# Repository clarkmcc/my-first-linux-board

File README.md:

# my-first-linux-board

`my-first-linux-board` is a small F1C200S Linux board built around removable microSD storage, USB-C power and USB device data, a 3.3 V UART console, and power/status LEDs. This repository contains the exact KiCad design used for the assembled board, the working Buildroot firmware source, the final JLCPCB fabrication package, and purchasing files.

The assembled board boots U-Boot 2026.01 and Linux 6.19.14 into a minimal BusyBox system. Both boot stages identify it as `Clark's Board`.

## Hardware

| Item | Final design |
|---|---|
| Processor | Allwinner F1C200S with 64 MiB integrated DDR1 |
| Board | 44 × 44 mm, four copper layers, R3 rounded corners |
| Power input | USB-C, 5 V, TPS2553 current-limited input switch |
| Rails | Three TPS62160 bucks for core, DDR, and I/O; TLV75528 analog LDO |
| Storage | Bottom-mounted microSD socket |
| Console | UART0 on a three-pin 3.3 V header: GND, TX, RX |
| USB | Native USB peripheral connection over USB-C |
| Indicators | Fixed power LED and PC0-controlled active-low status LED |
| Assembly | Components on top except the bottom microSD socket; through-hole UART header |
| Finish used | Black solder mask, white silkscreen, ENIG |

Open [hardware/boot-console.kicad_pro](hardware/boot-console.kicad_pro) in KiCad 10. The [BOM](hardware/docs/BOM.md), [pinout](hardware/docs/PINOUT.md), and [component-purpose guide](hardware/docs/COMPONENT-PURPOSE.md) describe the final circuit.

The [schematic PDF](docs/schematic.pdf) and [combined copper-layer image](docs/images/all-copper-layers.png) are convenient read-only views of the same final design.

## Firmware

The firmware directory is a Buildroot external tree. On macOS or another Docker host:

```sh
cd firmware
./build-container.sh
```

The complete card image is generated at:

```text
firmware/output/images/sdcard.img
```

The proven board configuration uses one-bit microSD transfers at 12.5 MHz. The physical board has four data traces, but Linux produced data errors in four-bit/25 MHz mode on the first assembly; the conservative setting boots reliably and is therefore the canonical configuration.

UART0 is 115200 baud, 8 data bits, no parity, and one stop bit. Linux also
creates a composite USB device with a CDC ACM console and a CDC ECM Ethernet
link. The board is `192.168.7.2/24`; its small DHCP server assigns the attached
host an address without advertising a default route or DNS server. On macOS,
the gadget can enumerate before Network Settings creates a service. Find the
interface whose MAC address is `02:00:00:00:07:01`, assign the host side
`192.168.7.1` for immediate access, and ask macOS to detect the new hardware:

```sh
iface=$(for interface in $(ifconfig -l); do
  ifconfig "$interface" | grep -q 'ether 02:00:00:00:07:01' && echo "$interface"
done)
sudo ifconfig "$iface" inet 192.168.7.1 netmask 255.255.255.0 up
sudo networksetup -detectnewhardware
```

This address lasts until the interface is removed or reconfigured. After
`networksetup -detectnewhardware` creates the service, give it the persistent
static address used by this direct link. The service on the tested Mac is named
`Clark's Board Console + Ethernet`:

```sh
sudo networksetup -setmanual "Clark's Board Console + Ethernet" \
  192.168.7.1 255.255.255.0 0.0.0.0
```

If macOS uses a different service name, find it with
`networksetup -listallnetworkservices` and substitute that name. DHCP did not
activate this ECM link reliably, so keep the host address static.

Prometheus metrics are the only HTTP resource. Scrape them with:

```sh
curl http://192.168.7.2/cgi-bin/metrics
```

The endpoint uses the Prometheus 0.0.4 text format and reports board identity,
time, CPU, load, memory, VM, pressure, filesystem, microSD, network, socket,
entropy, LED, service, USB gadget, and available thermal, CPU-frequency, and
watchdog data. The root URL and every other HTTP path intentionally return 404.

SSH is available as `root` with a blank password:

```sh
ssh root@192.168.7.2
```

This passwordless access is intended for a directly attached development
cable. The first boot stores a generated SSH host key on the FAT boot partition
so the host fingerprint remains stable while the read-only root stays unchanged.

The status LED appears at:

```text
/sys/class/leds/boot-console:green:status
```

It uses the CPU `activity` trigger by default. Manual control:

```sh
LED=/sys/class/leds/boot-console:green:status
echo none > "$LED/trigger"
echo 1 > "$LED/brightness"
echo 0 > "$LED/brightness"
```

See [firmware/README.md](firmware/README.md) for build details and [firmware/docs/BRINGUP.md](firmware/docs/BRINGUP.md) for bench bring-up.

## Manufacturing and purchasing

- [fabrication/clarks-board-JLCPCB-gerbers.zip](fabrication/clarks-board-JLCPCB-gerbers.zip) is the exact bare-board package used for the final revision.
- [fabrication/assembly/clarks-board-JLCPCB-BOM.csv](fabrication/assembly/clarks-board-JLCPCB-BOM.csv) and [fabrication/assembly/clarks-board-JLCPCB-CPL.csv](fabrication/assembly/clarks-board-JLCPCB-CPL.csv) are formatted for JLCPCB assembly upload.
- [procurement/DigiKey-order.csv](procurement/DigiKey-order.csv) and [procurement/LCSC-order.csv](procurement/LCSC-order.csv) contain the final supplier split used during sourcing.
- [hardware/assembly/ibom.html](hardware/assembly/ibom.html) is an interactive assembly view.

The fabrication package retains the routed board exactly. USB impedance was not matched to a specific JLCPCB controlled-impedance stackup, so select and verify a stackup before changing USB routing or ordering a controlled-impedance revision.

## Validation status

- The assembled board reaches a Linux login prompt over UART.
- The status LED works through the Linux LED subsystem after correcting duplicate PC0 pin ownership.
- KiCad ERC and DRC pass on the final source.
- The saved fabrication package matches the final KiCad source.
- Power/reset calculations and saved transient results are documented in [docs/POWER-VERIFICATION.md](docs/POWER-VERIFICATION.md).

Generated firmware images, Buildroot downloads, compiler output, KiCad backups, caches, and editor state are intentionally excluded from Git.

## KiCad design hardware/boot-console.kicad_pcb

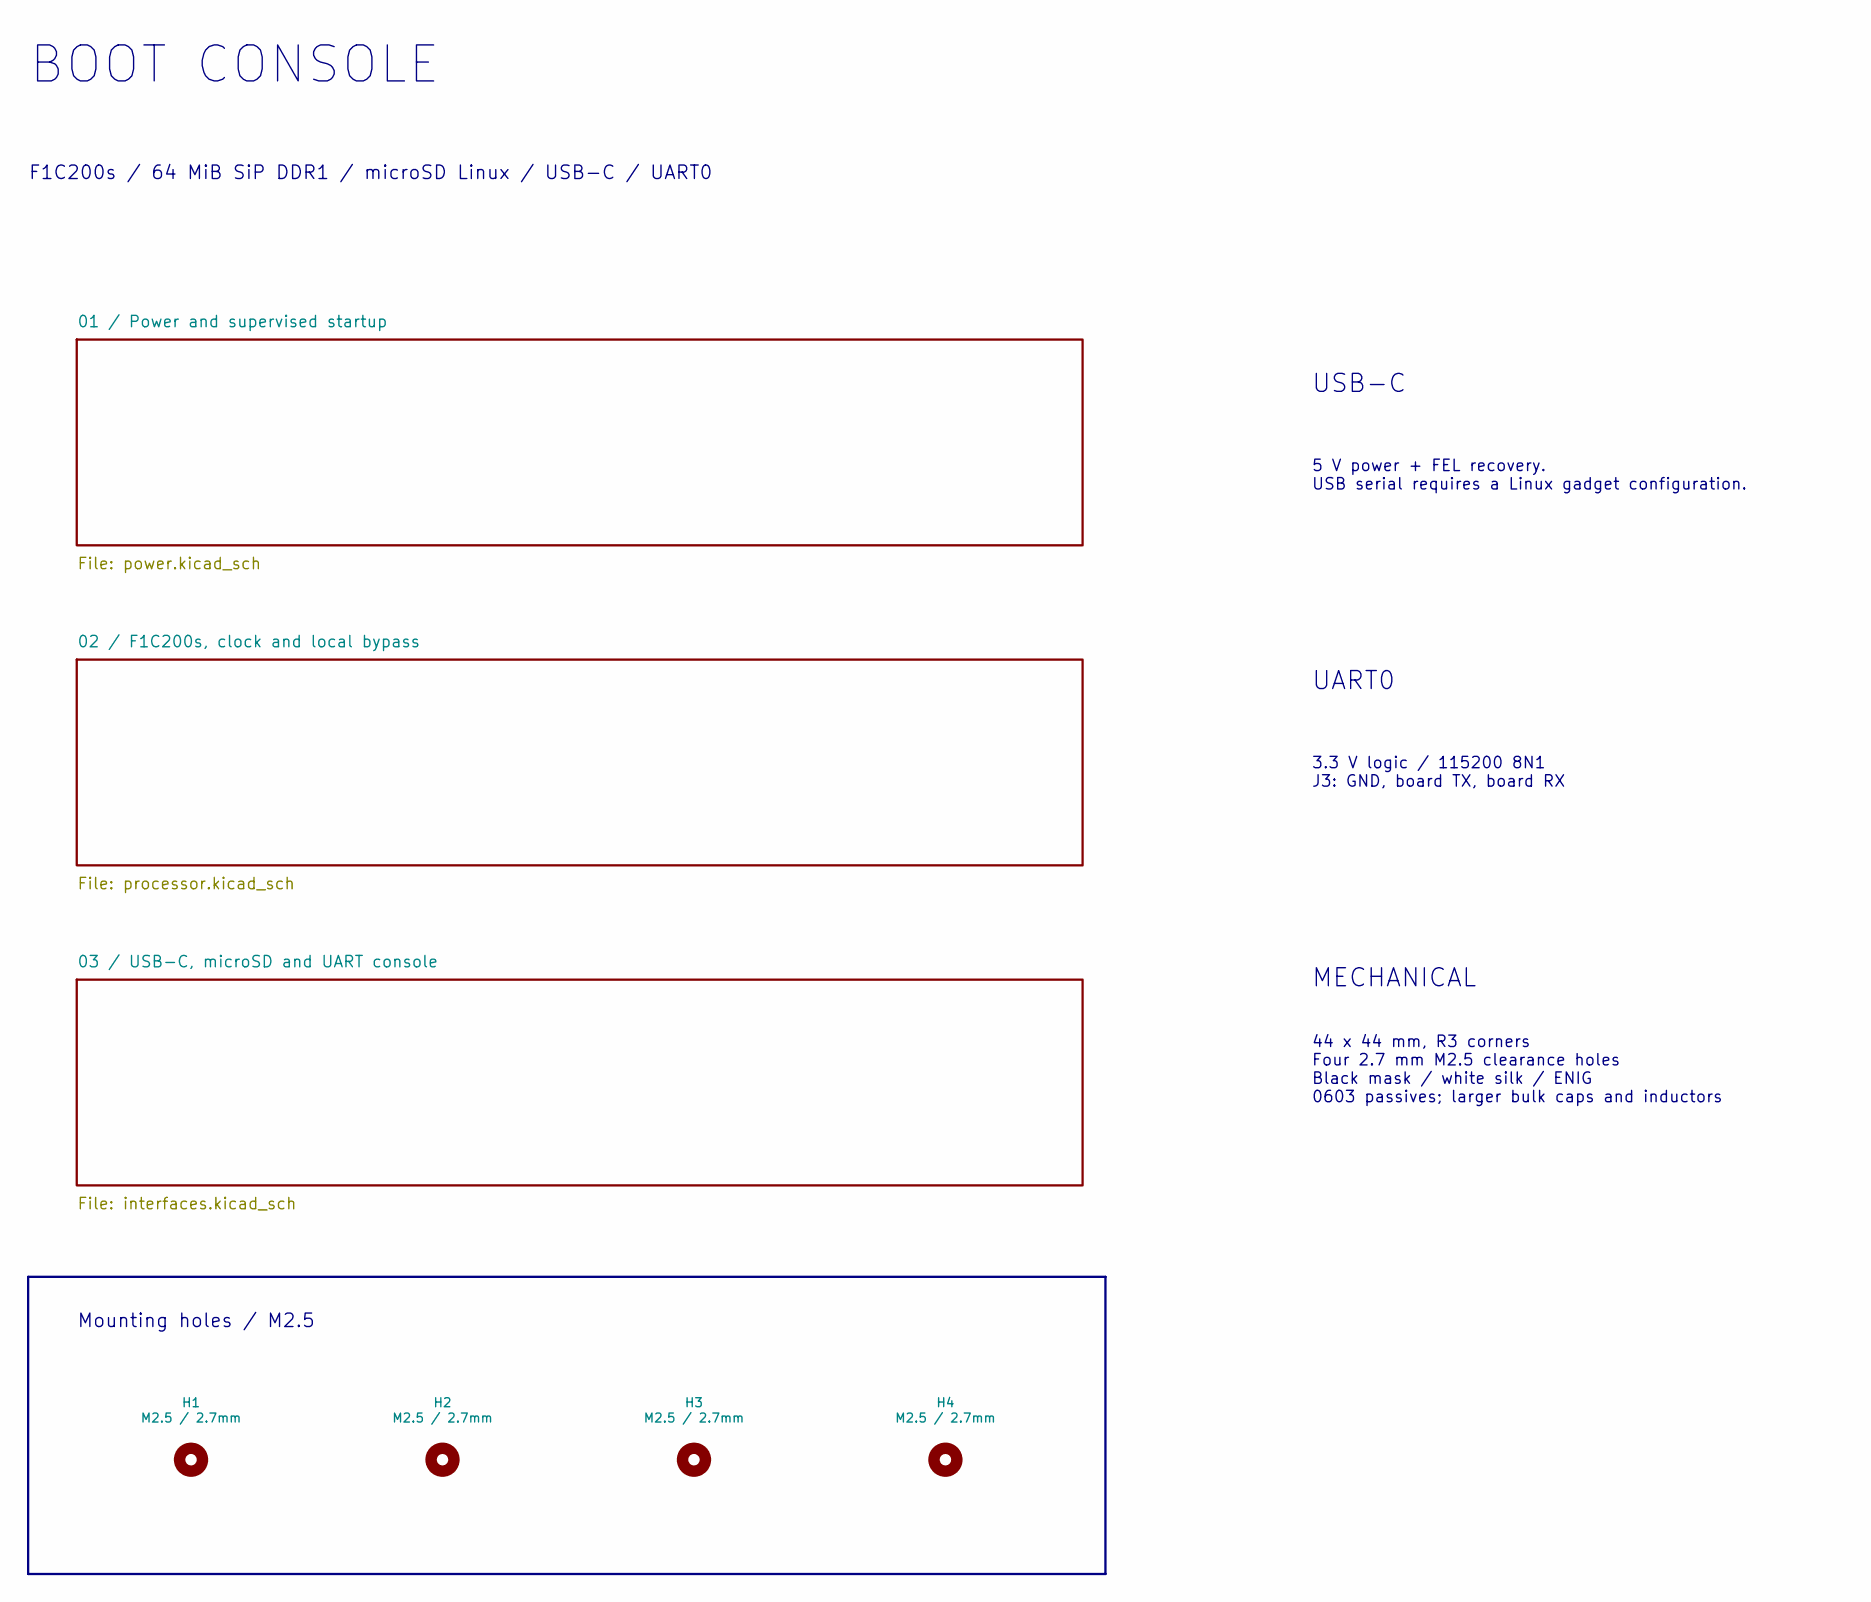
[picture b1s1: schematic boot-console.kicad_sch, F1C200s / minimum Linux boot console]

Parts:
H1, H2, H3, H4: M2.5 / 2.7mm; MountingHole_2.7mm_M2.5

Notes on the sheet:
BOOT CONSOLE
F1C200s / 64 MiB SiP DDR1 / microSD Linux / USB-C / UART0
USB-C
5 V power + FEL recovery. USB serial requires a Linux gadget configuration.
UART0
3.3 V logic / 115200 8N1 J3: GND, board TX, board RX
MECHANICAL
44 x 44 mm, R3 corners Four 2.7 mm M2.5 clearance holes Black mask / white silk / ENIG 0603 passives; larger bulk caps and inductors
Mounting holes / M2.5

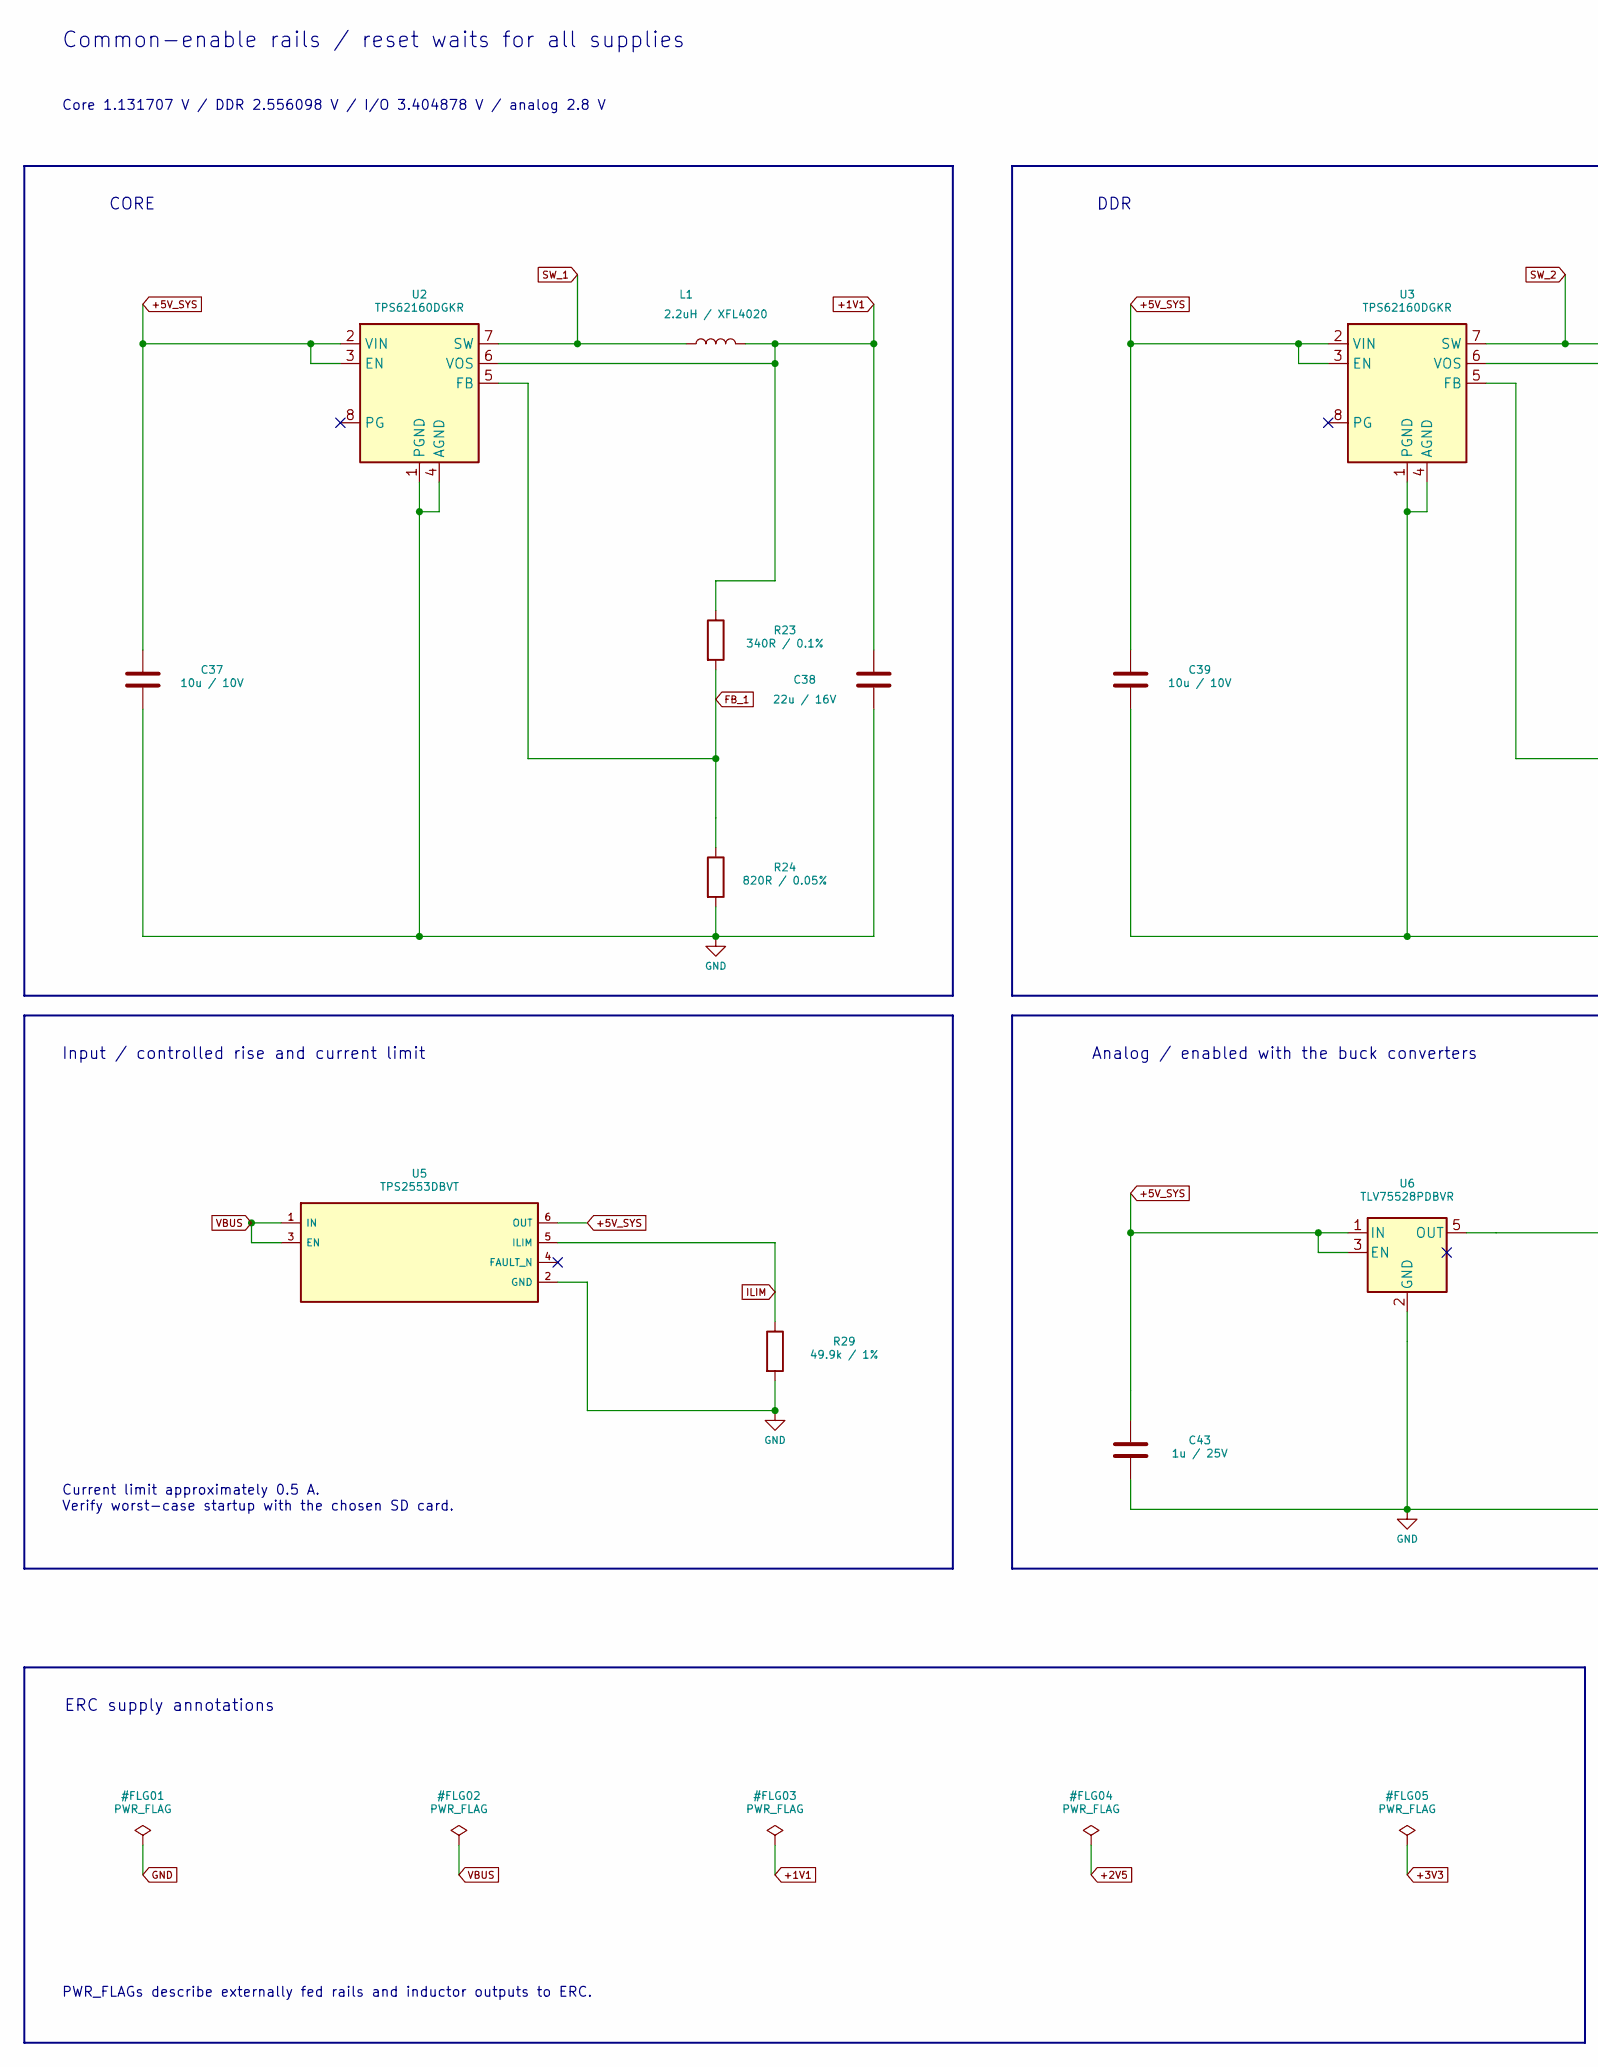
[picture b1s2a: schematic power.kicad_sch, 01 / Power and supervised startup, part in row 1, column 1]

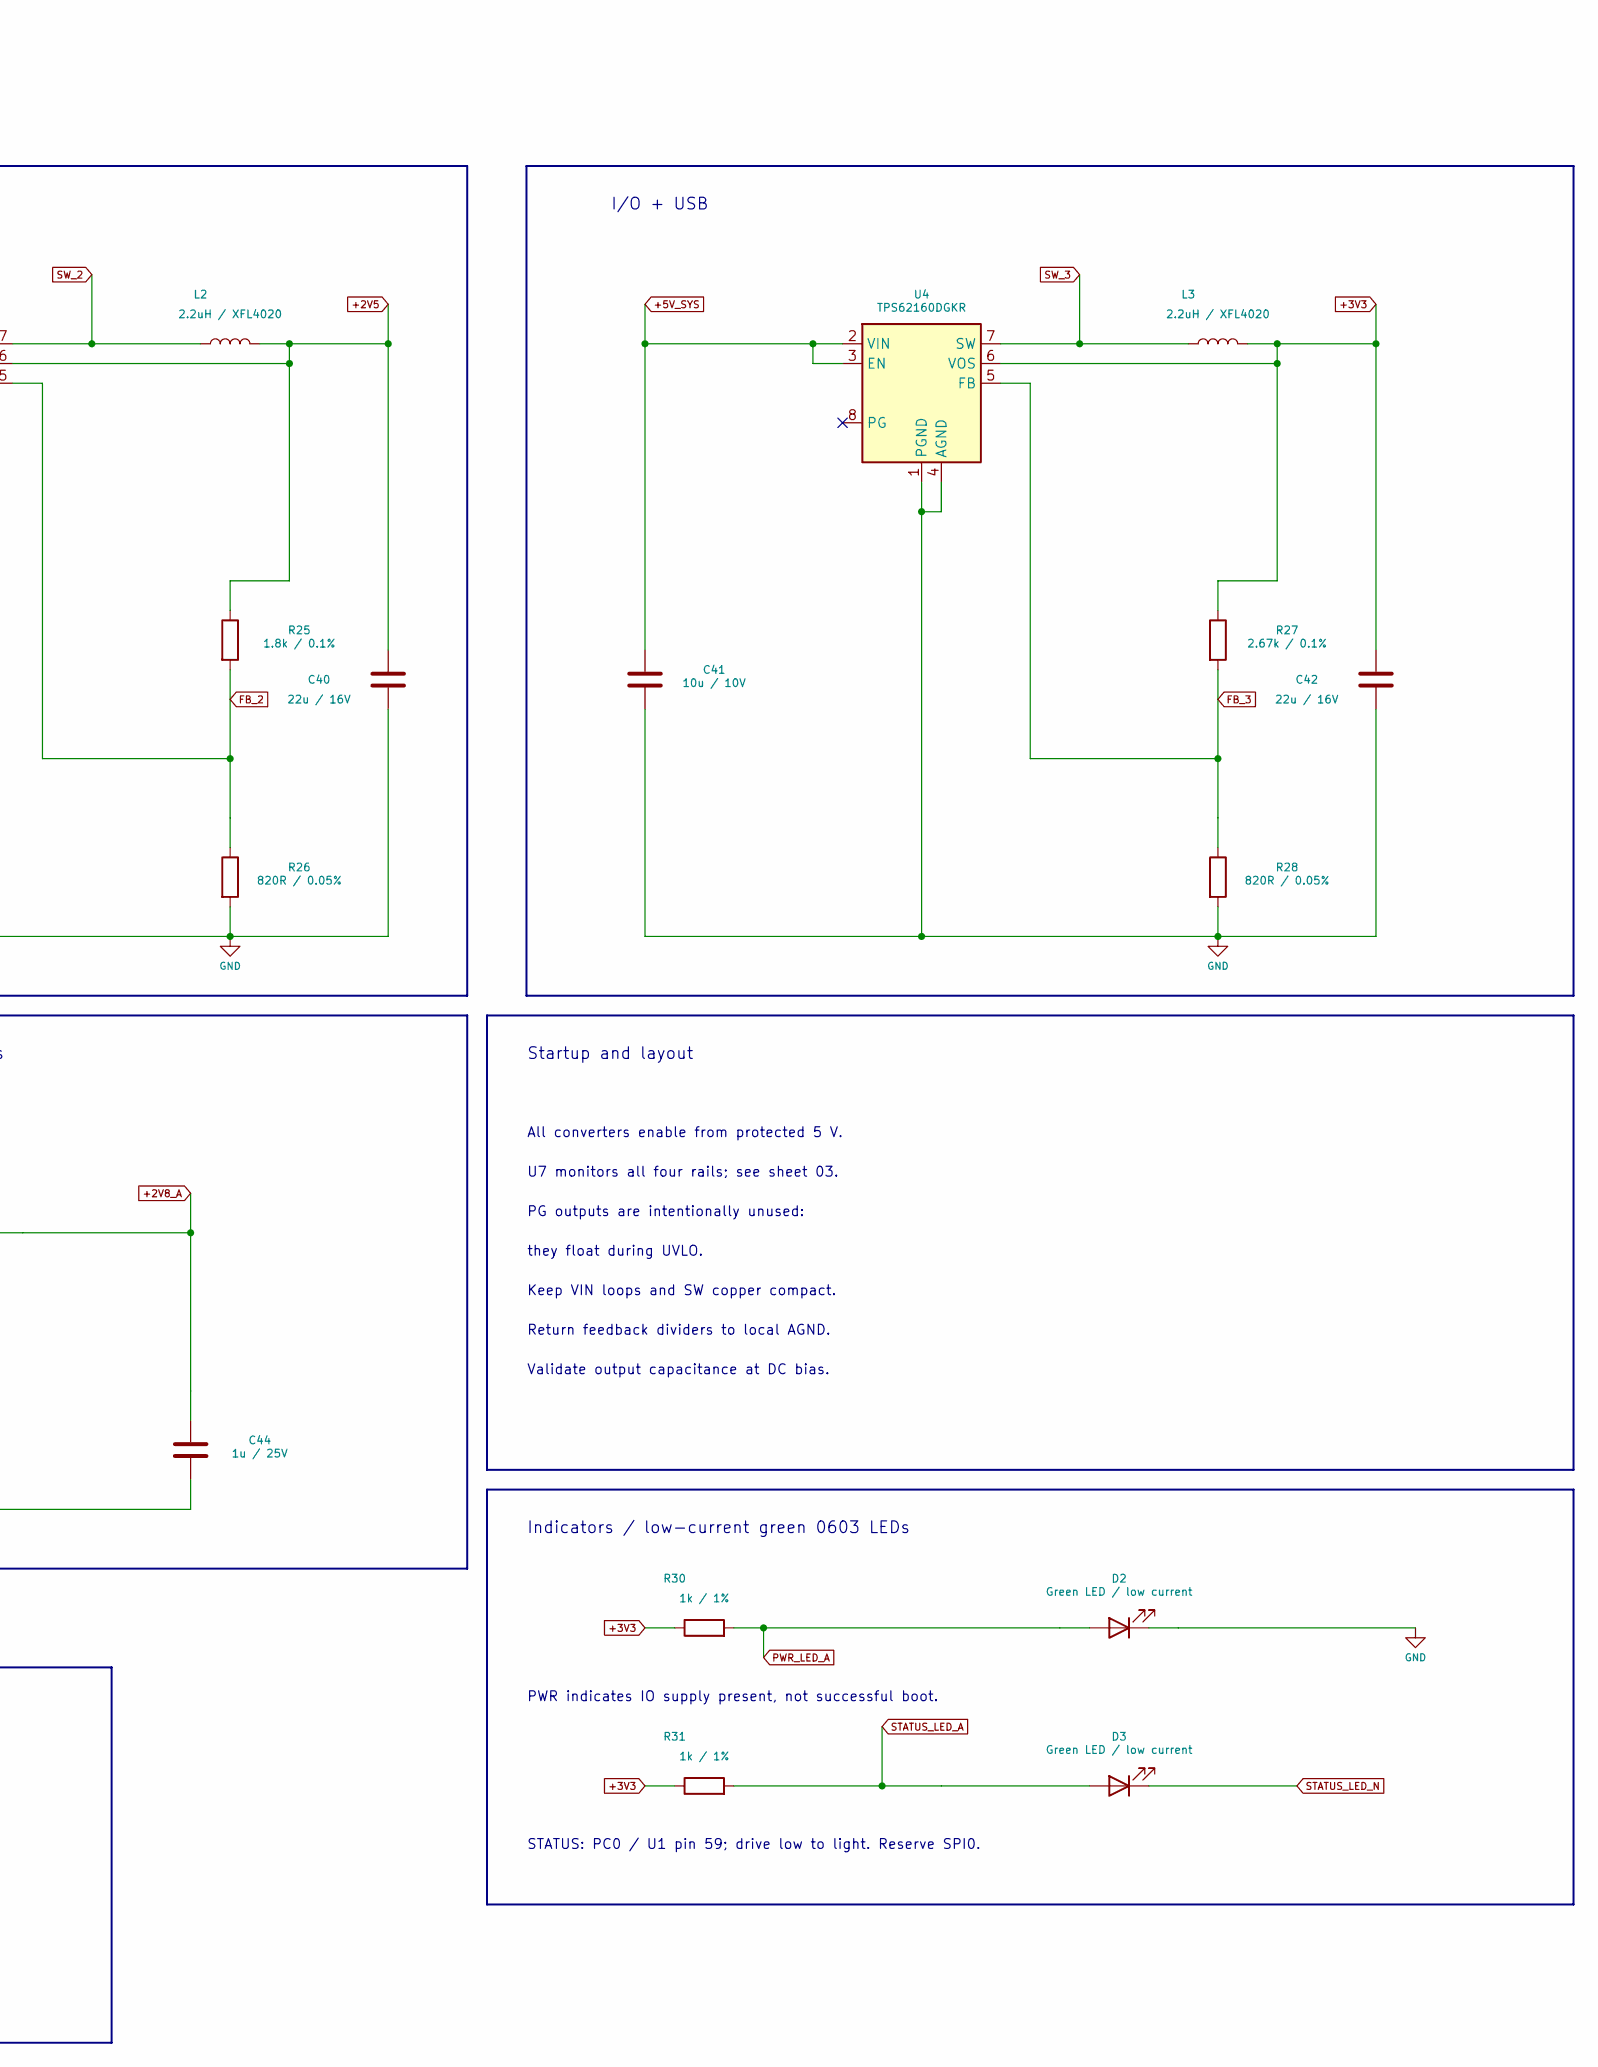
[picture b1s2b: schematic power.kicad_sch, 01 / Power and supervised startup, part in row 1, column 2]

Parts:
C37, C39, C41: 10u / 10V; C_0805_2012Metric; MPN C2012X5R1A106M085AB
C38, C40, C42: 22u / 16V; C_0805_2012Metric; MPN CL21A226MOCLRNC
C43, C44: 1u / 25V; C_0603_1608Metric; MPN C1608X7R1E105K080AB
D2, D3: Green LED / low current; LED_0603_1608Metric; MPN APT1608LZGCK
L1, L2, L3: 2.2uH / XFL4020; L_Coilcraft_XxL4020; MPN XFL4020-222MEC
R23: 340R / 0.1%; R_0603_1608Metric; MPN RT0603BRD07340RL
R24, R26, R28: 820R / 0.05%; R_0603_1608Metric; MPN RG1608N-821-W-T1
R25: 1.8k / 0.1%; R_0603_1608Metric; MPN RG1608P-182-B-T5
R27: 2.67k / 0.1%; R_0603_1608Metric; MPN RG1608P-2671-B-T5
R29: 49.9k / 1%; R_0603_1608Metric; MPN RC0603FR-0749K9L
R30, R31: 1k / 1%; R_0603_1608Metric; MPN RC0603FR-071KL
U2, U3, U4: TPS62160DGKR; MSOP-8_3x3mm_P0.65mm; MPN TPS62160DGKR
U5: TPS2553DBVT; SOT-23-6; MPN TPS2553DBVT
U6: TLV75528PDBVR; SOT-23-5; MPN TLV75528PDBVR

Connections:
+1V1: C38.1, L1.2, R23.1, U2.6 (VOS); also elsewhere on the board
+2V5: C40.1, L2.2, R25.1, U3.6 (VOS); also elsewhere on the board
+2V8_A: C44.1, U6.5 (OUT); also elsewhere on the board
+3V3: C42.1, L3.2, R27.1, R30.1, R31.1, U4.6 (VOS); also elsewhere on the board
+5V_SYS: C37.1, C39.1, C41.1, C43.1, U2.2 (VIN), U2.3 (EN), U3.2 (VIN), U3.3 (EN), U4.2 (VIN), U4.3 (EN), U5.6 (OUT), U6.1 (IN), U6.3 (EN)
FB_1: R23.2, R24.1, U2.5 (FB)
FB_2: R25.2, R26.1, U3.5 (FB)
FB_3: R27.2, R28.1, U4.5 (FB)
GND: C37.2, C38.2, C39.2, C40.2, C41.2, C42.2, C43.2, C44.2, D2.1 (K), R24.2, R26.2, R28.2, R29.2, U2.1 (PGND), U2.4 (AGND), U3.1 (PGND), U3.4 (AGND), U4.1 (PGND), U4.4 (AGND), U5.2 (GND), U6.2 (GND); also elsewhere on the board
ILIM: R29.1, U5.5 (ILIM)
PWR_LED_A: D2.2 (A), R30.2
STATUS_LED_A: D3.2 (A), R31.2
STATUS_LED_N: D3.1 (K); also elsewhere on the board
SW_1: L1.1, U2.7 (SW)
SW_2: L2.1, U3.7 (SW)
SW_3: L3.1, U4.7 (SW)
VBUS: U5.1 (IN), U5.3 (EN); also elsewhere on the board

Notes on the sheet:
ERC supply annotations
Common-enable rails / reset waits for all supplies
Core 1.131707 V / DDR 2.556098 V / I/O 3.404878 V / analog 2.8 V
CORE
DDR
I/O + USB
Input / controlled rise and current limit
Current limit approximately 0.5 A. Verify worst-case startup with the chosen SD card.
Analog / enabled with the buck converters
Startup and layout
All converters enable from protected 5 V.
U7 monitors all four rails; see sheet 03.
PG outputs are intentionally unused:
they float during UVLO.
Keep VIN loops and SW copper compact.
Return feedback dividers to local AGND.
Validate output capacitance at DC bias.
PWR_FLAGs describe externally fed rails and inductor outputs to ERC.
Indicators / low-current green 0603 LEDs
PWR indicates IO supply present, not successful boot.
STATUS: PC0 / U1 pin 59; drive low to light. Reserve SPI0.

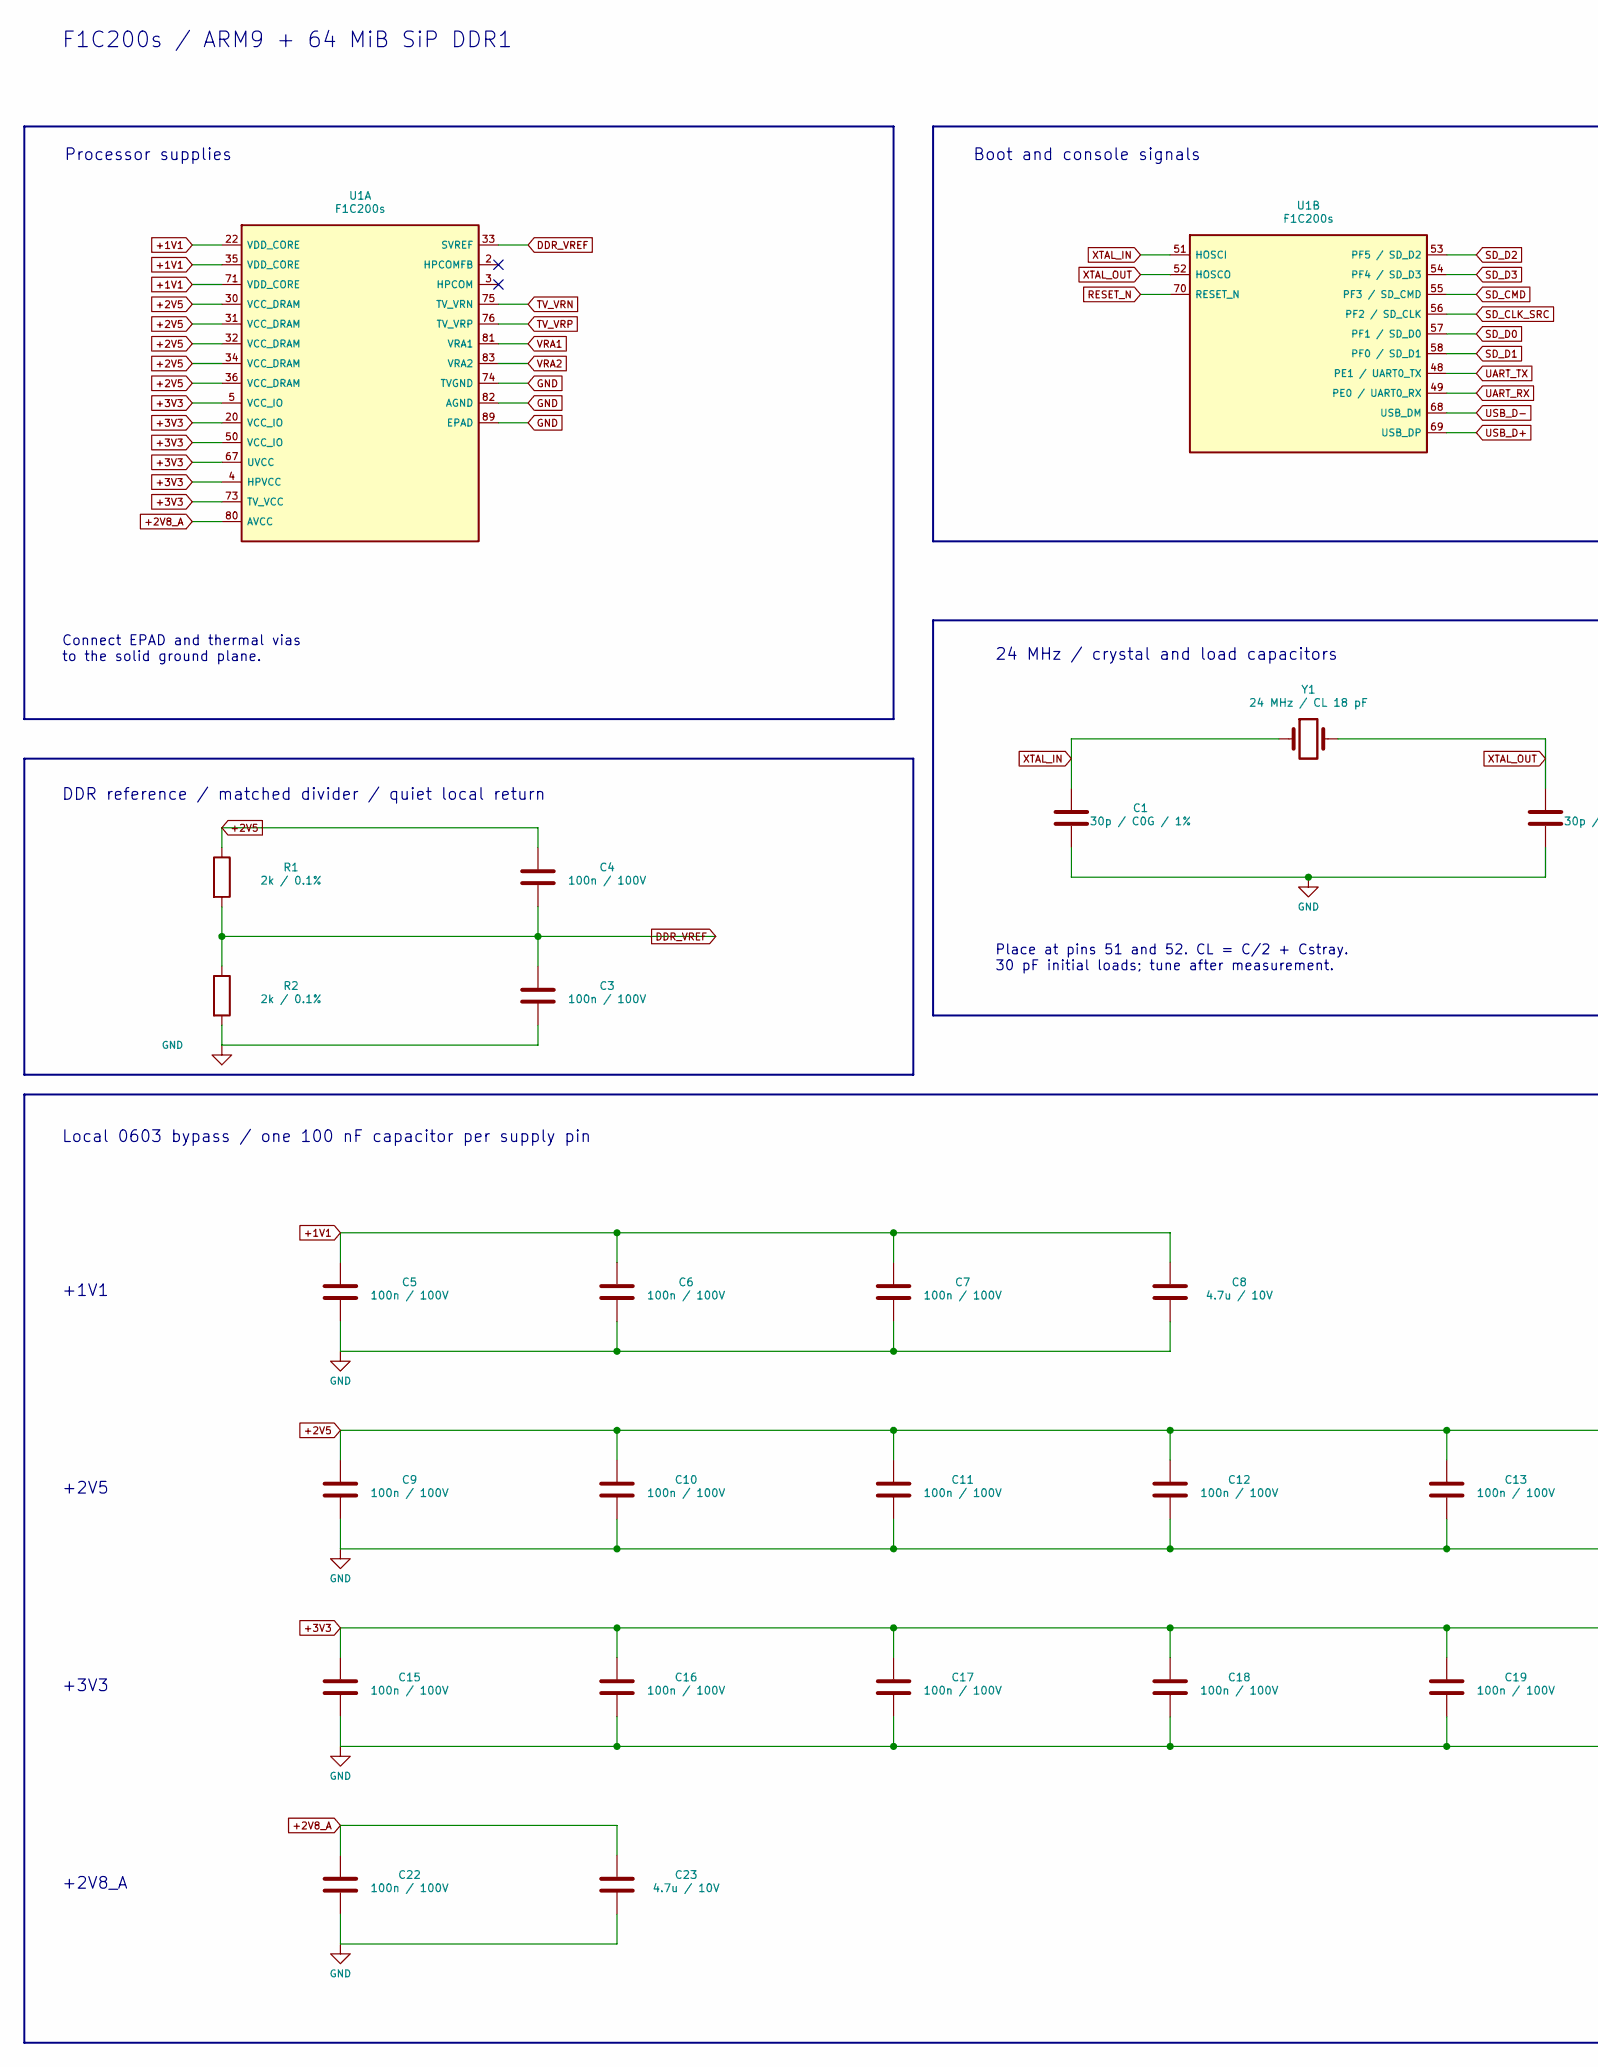
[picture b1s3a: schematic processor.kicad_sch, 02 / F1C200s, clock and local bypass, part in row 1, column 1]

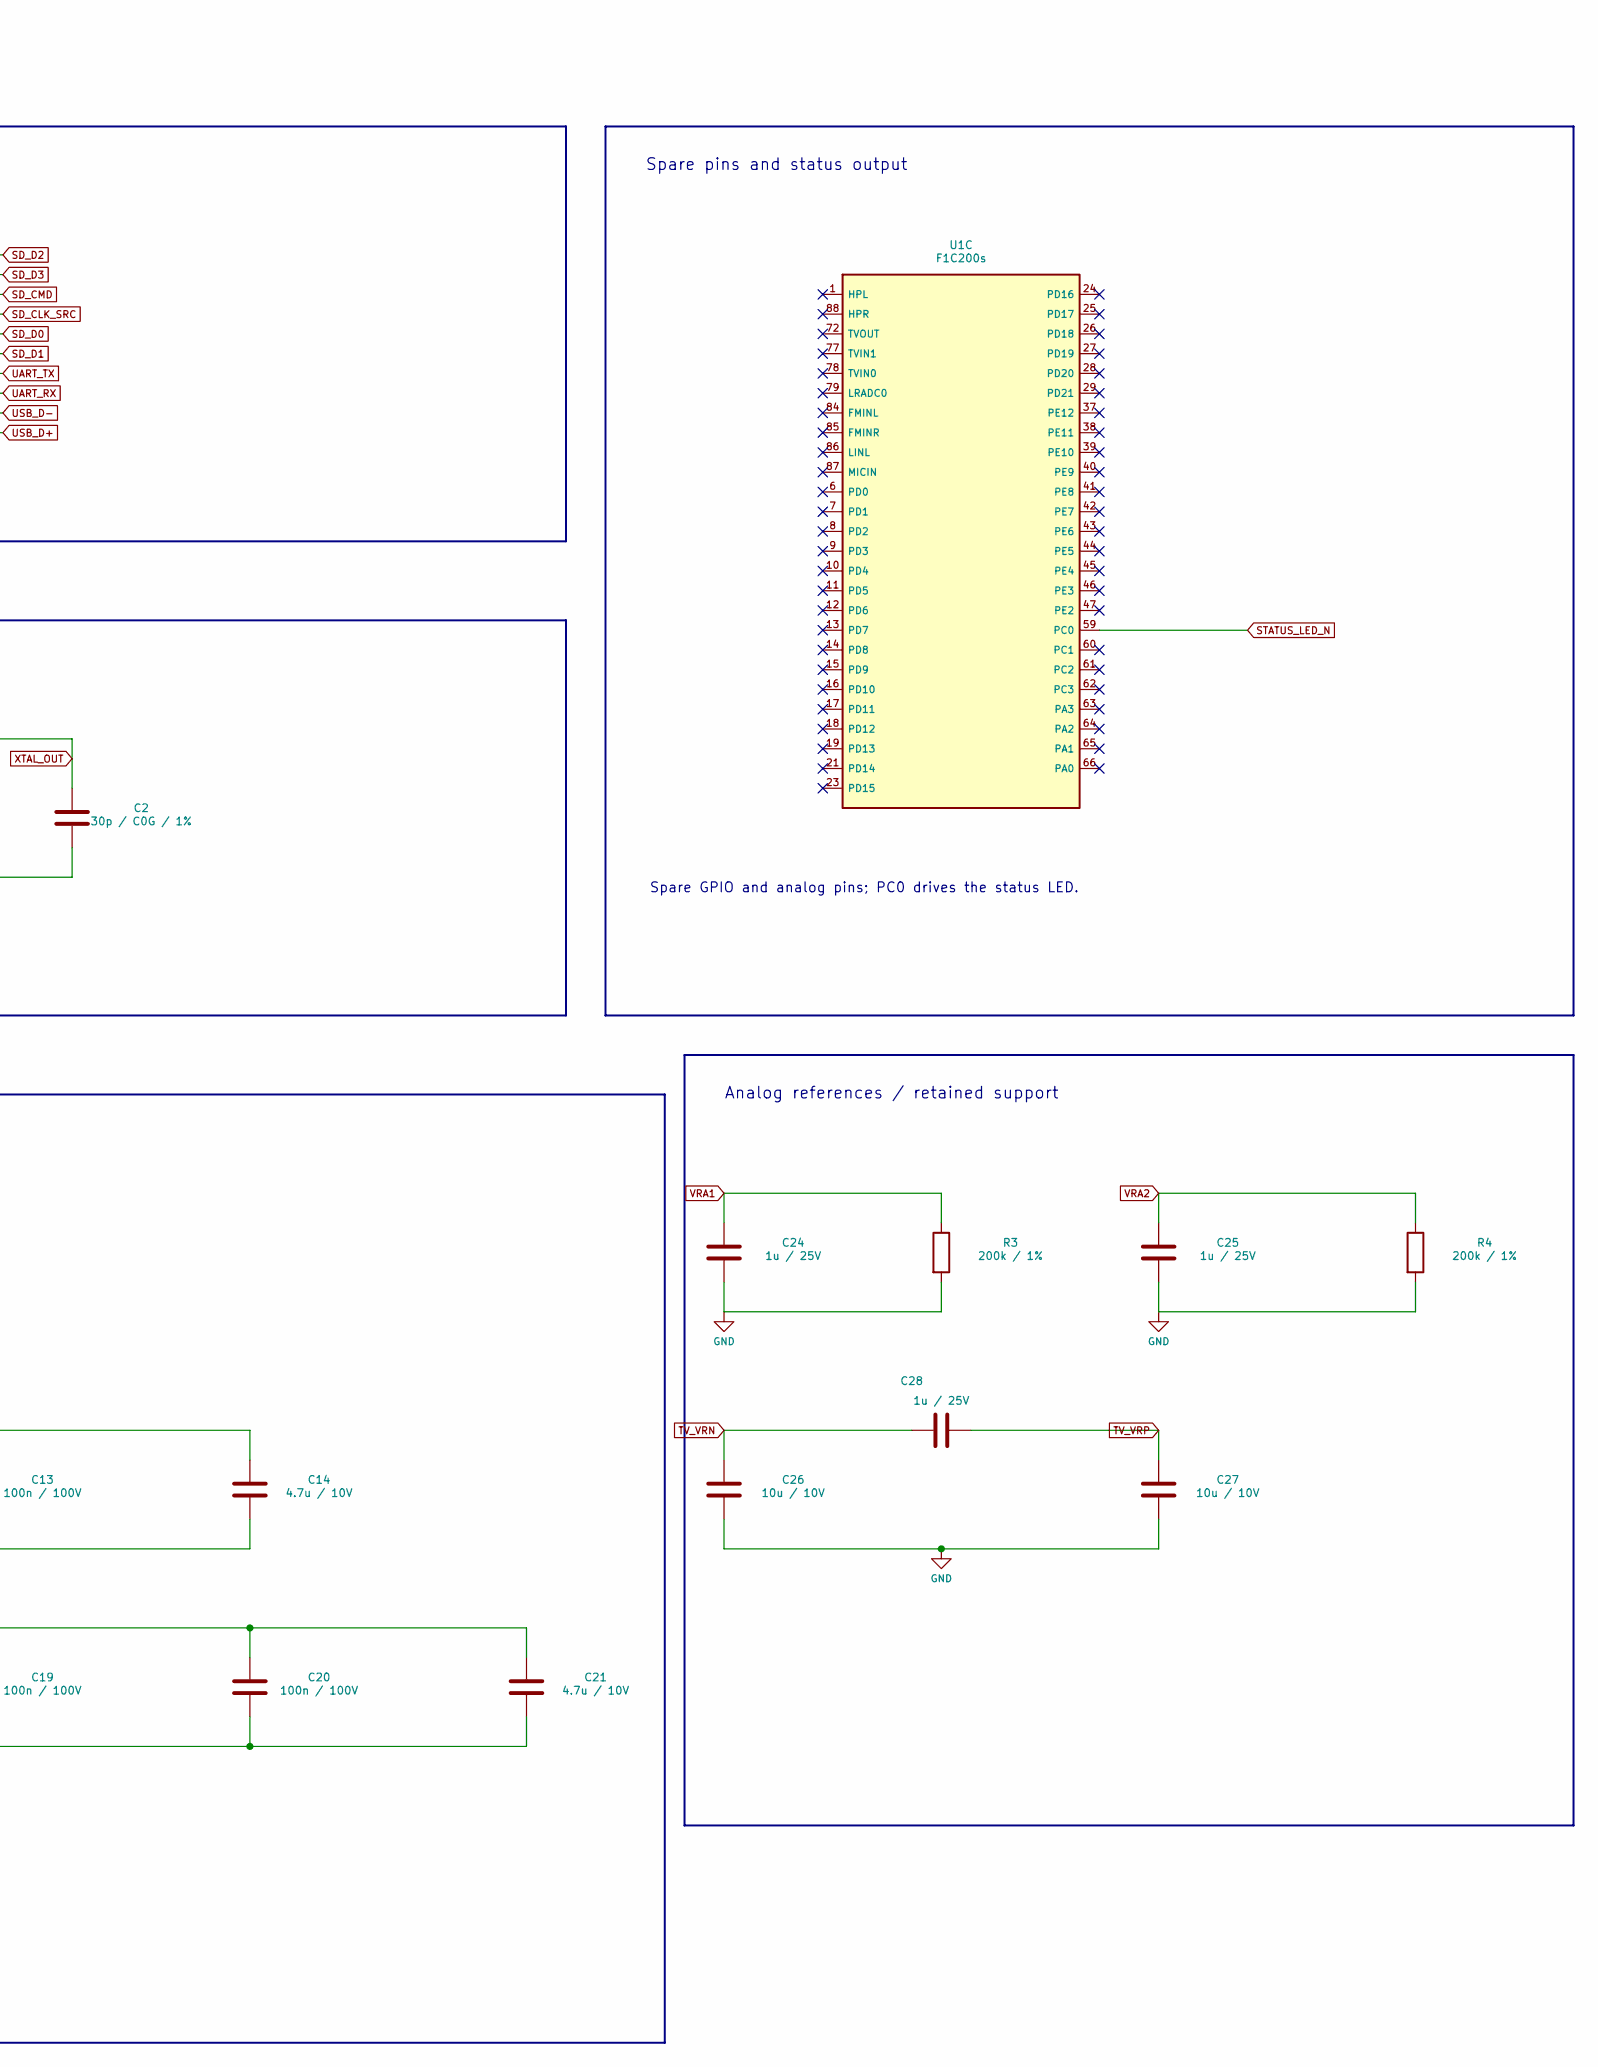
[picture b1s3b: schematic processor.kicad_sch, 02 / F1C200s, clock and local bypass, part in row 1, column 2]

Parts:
C1, C2: 30p / C0G / 1%; C_0603_1608Metric; MPN C0603C300F5GACTU
C3, C4, C5, C6, C7, C9, C10, C11, C12, C13, C15, C16, C17, C18, C19, C20, C22: 100n / 100V; C_0603_1608Metric; MPN GRM188R72A104KA35D
C8, C14, C21, C23: 4.7u / 10V; C_0603_1608Metric; MPN GRM188R61A475KE15D
C24, C25, C28: 1u / 25V; C_0603_1608Metric; MPN C1608X7R1E105K080AB
C26, C27: 10u / 10V; C_0805_2012Metric; MPN C2012X5R1A106M085AB
R1, R2: 2k / 0.1%; R_0603_1608Metric; MPN RG1608P-202-B-T5
R3, R4: 200k / 1%; R_0603_1608Metric; MPN RC0603FR-07200KL
U1: F1C200s; F1C200s_QFN88_10x10_P0.4_EP6.74; MPN F1C200S
Y1: 24 MHz / CL 18 pF; Raltron_H130A_5032; MPN H130A-24.000-18-2030-EXT-TR

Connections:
+1V1: C5.1, C6.1, C7.1, C8.1, U1.22 (VDD_CORE), U1.35 (VDD_CORE), U1.71 (VDD_CORE); also elsewhere on the board
+2V5: C4.1, C9.1, C10.1, C11.1, C12.1, C13.1, C14.1, R1.1, U1.30 (VCC_DRAM), U1.31 (VCC_DRAM), U1.32 (VCC_DRAM), U1.34 (VCC_DRAM), U1.36 (VCC_DRAM); also elsewhere on the board
+2V8_A: C22.1, C23.1, U1.80 (AVCC); also elsewhere on the board
+3V3: C15.1, C16.1, C17.1, C18.1, C19.1, C20.1, C21.1, U1.4 (HPVCC), U1.5 (VCC_IO), U1.20 (VCC_IO), U1.50 (VCC_IO), U1.67 (UVCC), U1.73 (TV_VCC); also elsewhere on the board
DDR_VREF: C3.1, C4.2, R1.2, R2.1, U1.33 (SVREF)
GND: C1.2, C2.2, C3.2, C5.2, C6.2, C7.2, C8.2, C9.2, C10.2, C11.2, C12.2, C13.2, C14.2, C15.2, C16.2, C17.2, C18.2, C19.2, C20.2, C21.2, C22.2, C23.2, C24.2, C25.2, C26.2, C27.2, R2.2, R3.2, R4.2, U1.74 (TVGND), U1.82 (AGND), U1.89 (EPAD); also elsewhere on the board
RESET_N: U1.70 (RESET_N); also elsewhere on the board
SD_CLK_SRC: U1.56 (PF2 / SD_CLK); also elsewhere on the board
SD_CMD: U1.55 (PF3 / SD_CMD); also elsewhere on the board
SD_D0: U1.57 (PF1 / SD_D0); also elsewhere on the board
SD_D1: U1.58 (PF0 / SD_D1); also elsewhere on the board
SD_D2: U1.53 (PF5 / SD_D2); also elsewhere on the board
SD_D3: U1.54 (PF4 / SD_D3); also elsewhere on the board
STATUS_LED_N: U1.59 (PC0); also elsewhere on the board
TV_VRN: C26.1, C28.2, U1.75 (TV_VRN)
TV_VRP: C27.1, C28.1, U1.76 (TV_VRP)
UART_RX: U1.49 (PE0 / UART0_RX); also elsewhere on the board
UART_TX: U1.48 (PE1 / UART0_TX); also elsewhere on the board
USB_D+: U1.69 (USB_DP); also elsewhere on the board
USB_D-: U1.68 (USB_DM); also elsewhere on the board
VRA1: C24.1, R3.1, U1.81 (VRA1)
VRA2: C25.1, R4.1, U1.83 (VRA2)
XTAL_IN: C1.1, U1.51 (HOSCI), Y1.1
XTAL_OUT: C2.1, U1.52 (HOSCO), Y1.2

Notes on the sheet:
Processor supplies
Boot and console signals
Spare pins and status output
F1C200s / ARM9 + 64 MiB SiP DDR1
Spare GPIO and analog pins; PC0 drives the status LED.
Connect EPAD and thermal vias to the solid ground plane.
24 MHz / crystal and load capacitors
Place at pins 51 and 52. CL = C/2 + Cstray. 30 pF initial loads; tune after measurement.
DDR reference / matched divider / quiet local return
Local 0603 bypass / one 100 nF capacitor per supply pin
+1V1
+2V5
+3V3
+2V8_A
Analog references / retained support
